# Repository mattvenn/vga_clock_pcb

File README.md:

Matt Venn's ASIC VGA Clock
==========================

* World's first [certified open source hardware](https://certification.oshwa.org/es000023.html) down to the GDS?
* The ASIC was part of the Google sponsored MPW1
* The ASIC is still in fabrication by Skywater, we expect silicon in September 2021.
* For more details about the implementation, see [VGA ASIC Clock](https://www.zerotoasiccourse.com/post/vga_clock/). 
* RTL: https://github.com/mattvenn/vga-clock
* Application details: https://efabless.com/projects/14

# PCB

This PCB provides all the necessary components to make a functional clock:

 * Pads for mounting the ASIC
 * Decoupling
 * Voltage regulators for core (1.8) and IO (3.3)
 * Crystal oscillator
 * SOIC-8 footprint for dual SPI flash for the configuration firmware
 * 2x6 1.27mm header with housekeeping SPI, UART and 5V - the minimum connection needed for power and debug
 * [PDF Schematic](rev0.1/carrier.pdf)

# Setup

## Firmware

Needs to active project 2. See https://github.com/mattvenn/caravel-mph/blob/release/verilog/dv/caravel/user_proj_example/vga-clock/vga_clock.c for the simulation test.
Will need PLL setup to work on the ASIC.

## Flashing

For flashing, see https://github.com/efabless/ravenna/blob/master/firmware/blink/Makefile as a starting point. ravenna_hkspi.py may need some tweaks to work with Caravel.

The [SPI interface can be used to put the ASIC into 'passthrough' mode](https://caravel-harness.readthedocs.io/en/latest/housekeeping-spi.html#housekeeping-spi-command-words). Then the FLASH can be programmed through this same SPI interface.

See the schematic for the pinout of the SPI interface on the board.

## PLL config

Needs 31.5MHz for VGA signal. As precise as possible for good timekeeping.
Input oscillator is 9MHz.

Using https://github.com/kbeckmann/caravel-pll-calculator

    matt-desktop:2003 [main]: ./caravel_pll.py generate --clkout 31.5 --clkin 9
    PLL Parameters:

    clkin:    9.00 MHz
    clkout:   31.50 MHz
    clkout90: 31.50 MHz

    PLL Feedback Divider: 14
    PLL Output Divider 1: 4
    PLL Output Divider 2: 4

    Register 0x11: 0x24
    Register 0x12: 0x0e

## Pinning

See the instantiation into the user project area here: https://github.com/mattvenn/multi-project-harness/blob/separate-macro/user_project_wrapper.v#L190
See the design repository here: https://github.com/mattvenn/vga-clock/tree/db029c38607c8d27f54b48bd8fd423cae3c4ed3d

    vga_clock proj_2 (
        .clk(proj2_clk),
        .reset_n(proj2_reset),
        .adj_hrs(proj2_io_in[8]),
        .adj_min(proj2_io_in[9]),
        .adj_sec(proj2_io_in[10]),
        .hsync(proj2_io_out[11]),
        .vsync(proj2_io_out[12]),
        .rrggbb(proj2_io_out[18:13])
        );

* rrggbb is mapped to R1, R2, G1, G2, B1, B2
* 500R used for R1, G1, B1
* 1k used for R2, G2, B2

## Power

### User project

* Power is provided to the clock design only by VCCD1 and VSSD1.
* Tim Edwards suggests:
    * keeping VCCD2 and VCCD1, VSSD2 and VSSD1 tied together just to make sure there are no floating power supplies.  
    * connect VDDA1 and VDDA2 to VDDIO, and VSSA1 and VSSA2 to VSSIO to make sure they're not floating.  
For reference, the power ring around the user project area has 4 buses. From outside to inside:  VSSA2, VDDA2, VSSA1, VDDA1, VSSD2, VCCD2, VSSD1, VCCD1.
    * VSSA2 user area 2 ground
    * VDDA2 3.3V user area 2 psu
    * VSSA1 user area 1 ground
    * VDDA1 3.3V user area 1 psu
    * VSSD2 user area 2 digital ground
    * VCCD2 1.8V user area 2 digital psu
    * VSSD1 user area 1 digital ground
    * VCCD1 1.8V user area 1 digital psu

### Management

* VDDIO/VSSIO   power and ground for IO (up to 5v). I'm connecting to 3.3v
* VDDA/VSSA     3.3v PSU for management area
* VCCD/VSSD     1.8v PSU for management area

# BOM

All available from digikey as of 13/7/21

* regulators
    * 1.8v MCP1824T-1802E/OT
    * 3.3v MIC5504-3.3YM5-TR
* flash: W25Q32JVSSIQ-TR
* oscillator: SIT8008AI-23-33S-9.000000 
* VGA connector: L77HDE15SD1CH4F
* USB connector: 1050170001
* buttons: PTS636 SM25J SMTR LFS

# Errata

## v0.1

* Initial footprint for ASIC was flipped. 
* All other components were tested and worked as expected.

## v0.2

* TBD

# Resources

* PCB forked from https://github.com/samlittlewood/caravel_carrier
* Caravel datasheet: https://caravel-harness.readthedocs.io/en/latest
* Logo created at: http://oshwmark.capablerobot.com/
* PCBs sponsored by https://OSHPark.com

# License

* The PCB is licensed under the [MIT License](LICENSE)
* The ASIC is licensed under the [Apache2 License](https://github.com/mattvenn/vga-clock/blob/master/LICENSE-2.0.txt)
* The documentation is licensed under the [CC0 License](CC0_license)

# Open Source Hardware

This board is an OSHWA approved design: [ES000023](https://certification.oshwa.org/es000023.html)

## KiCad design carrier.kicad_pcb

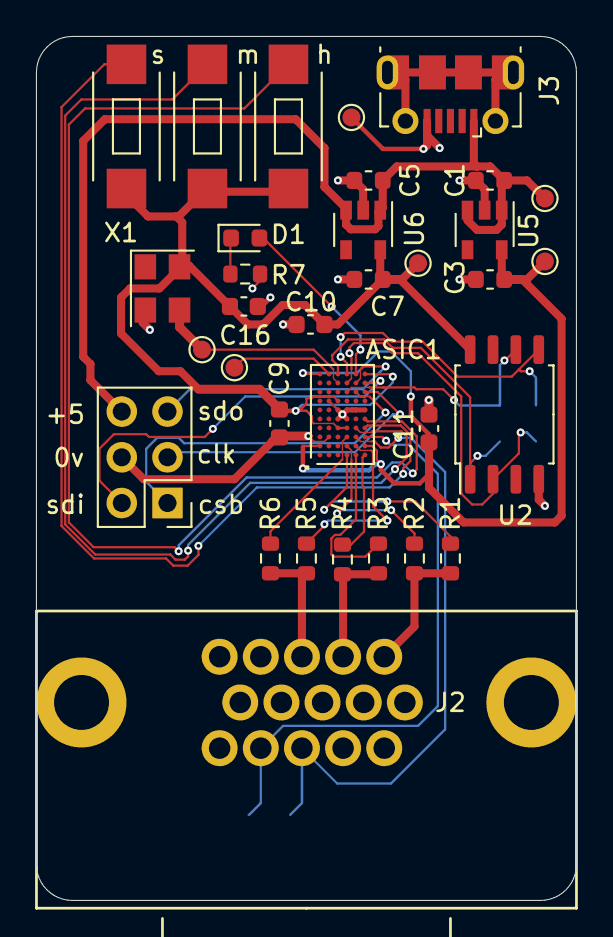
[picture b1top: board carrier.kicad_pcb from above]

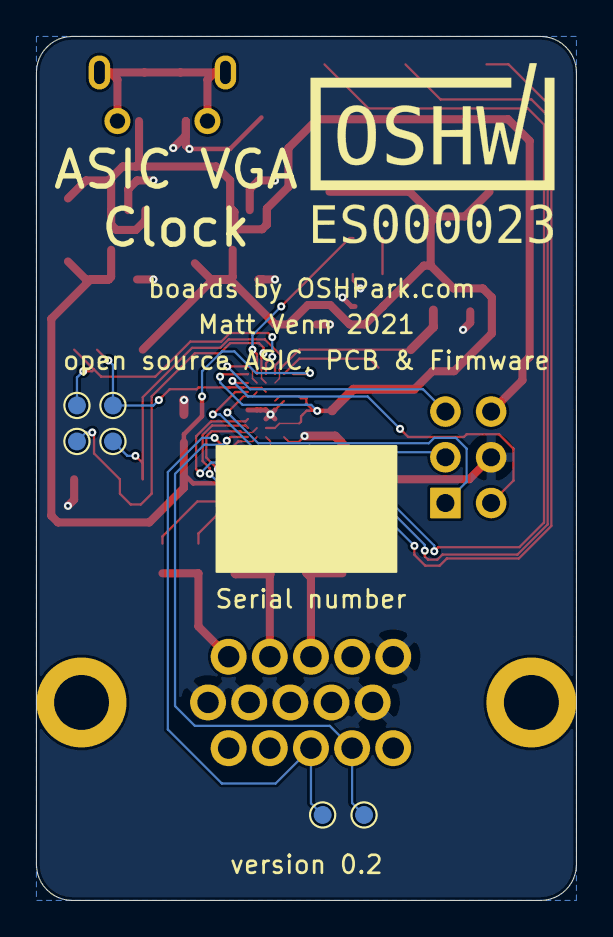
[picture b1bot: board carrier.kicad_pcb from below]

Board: 2 copper layers, 30.0 x 48.0 mm, 39 parts (6 on the bottom side), 30 nets.

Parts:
ASIC1: CARAVEL; WLCSP-60_P0.5mm
C1, C5: 1u 16v; C_0603_1608Metric
C3, C7: 4u7 16v; C_0603_1608Metric
C9, C10, C11, C16: 22n; C_0603_1608Metric
D1: LED; LED_0603_1608Metric
J1: Conn_02x03_Counter_Clockwise; PinHeader_2x03_P2.54mm_Vertical
J2: DB15_Female_HighDensity; db15
J3: USB_B_Micro; USB_Micro-B_Molex-105017-0001
R1, R3, R5: 500R; R_0603_1608Metric
R2, R4, R6: 1k; R_0603_1608Metric
R7: 100R; R_0603_1608Metric
SW1: SW_Push_hrs; pts636
SW2: SW_Push_min; pts636
SW3: SW_Push_sec; pts636
TP1, TP2, TP3, TP4, TP5, TP6, TP7, TP8, TP9, TP10, TP11, TP12: TestPoint; TestPoint_Pad_D1.0mm
U2: W25Q32JVSSIQ-TR; SOIC-8_5.23x5.23mm_P1.27mm
U5: MCP1824T-1802E/OT; SOT-23-5
U6: MIC5504-3.3YM5-TR; SOT-23-5
X1: ECS-5032MV-100-BN-TR; Oscillator_SMD_SeikoEpson_SG8002CE-4Pin_3.2x2.5mm

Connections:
+5V: C1.1, C5.1, J1.6, J3.1, TP10.1, U5.1, U5.3, U6.1, U6.3
/blue: J2.3, R5.1, R6.1
/green: J2.2, R3.1, R4.1
/red: J2.1, R1.1, R2.1
GND: ASIC1.B3, ASIC1.B7, ASIC1.C5, ASIC1.C6, ASIC1.D5, ASIC1.D6, ASIC1.E6, ASIC1.F6, C1.2, C3.2, C5.2, C7.2, C9.2, C10.2, C11.2, C16.2, J1.4, J2.5, J2.6, J2.7, J2.8, J2.10, J3.5, R7.2, TP12.1, U2.4, U5.2, U6.2, X1.2
unnamed: D1.1, R7.1
clock: ASIC1.C9, TP6.1, X1.3
flash_clk: ASIC1.D8, TP2.1, U2.6
flash_csb: ASIC1.C10, TP3.1, U2.1
flash_io0: ASIC1.D10, TP4.1, U2.5
flash_io1: ASIC1.D9, TP5.1, U2.2
gpio: ASIC1.E10, D1.2
mprj_io[1]: ASIC1.E9, J1.5
mprj_io[2]: ASIC1.F9, J1.2
mprj_io[3]: ASIC1.E8, J1.1
mprj_io[4]: ASIC1.F8, J1.3
mprj_io[8]: ASIC1.F5, SW1.1
mprj_io[9]: ASIC1.E4, SW2.1
mprj_io[10]: ASIC1.F4, SW3.1
mprj_io[11]: ASIC1.E3, J2.13, TP7.1
mprj_io[12]: ASIC1.F3, J2.14, TP8.1
mprj_io[13]: ASIC1.D3, R6.2
mprj_io[14]: ASIC1.E2, R5.2
mprj_io[15]: ASIC1.F1, R4.2
mprj_io[16]: ASIC1.E1, R3.2
mprj_io[17]: ASIC1.D2, R2.2
mprj_io[18]: ASIC1.D1, R1.2
resetb: ASIC1.B10, TP1.1
vccd: ASIC1.A2, ASIC1.A10, ASIC1.F2, C3.1, C11.1, TP9.1, U5.5
vdda: ASIC1.C4, ASIC1.C7, ASIC1.D4, ASIC1.F10, C7.1, C9.1, C10.1, C16.1, SW1.2, SW2.2, SW3.2, TP11.1, U2.8, U6.5, X1.4

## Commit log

2020-11-21 Add kicad files.
2020-11-21 Added README
2020-11-21 Missing files.
2020-11-21 Fix README.
2020-11-21 Add note about JLCPCB.
2020-11-23 Tidy up and ground pours.
2020-11-23 Updated plots.
2020-11-23 Tidy up regulators.
2020-11-23 Flipped to have regulators at top, makes pin/io number a better match.
2020-11-23 Tidy up power routing.
2020-11-23 Tidy up oscillator.
2020-11-23 Solder mask clearance.
2020-11-24 Use 1.27mm header.
2020-11-27 Clean up clearances.
2020-12-18 Use 5mil for inner layers.
2020-12-18 Correct directions on global labels.
2020-12-20 Update gerbers & pdf.
2020-12-23 Make wlcsp escape 3mil/3mil.
2020-12-23 Made rest of board 4mil/4mil.
2020-12-23 New output files.
2021-04-17 Update README.md
    make it more discoverable with searches. I tried all variants of pcb, shuttle, asic, caravel, efabless and couldn't find it!
2021-07-06 updating for vga clock
2021-07-06 fp for vga
2021-07-06 pdf of schematic
2021-07-06 updated pcb
2021-07-06 format
2021-07-06 docs and license. fix db15 fp, add oshw logo
2021-07-06 include pics
2021-07-06 pics
2021-07-06 gerbers
2021-07-06 questions
2021-07-06 routing and silk improvements, added an led to GPIO
2021-07-06 updated pdf
2021-07-06 DAC ladder updated
2021-07-06 continue to tweak layout
2021-07-13 all BOM parts found on digikey, button footprint
2021-07-23 ES000023 OSHW registration
2021-07-23 updated board with OSHW mark
2021-07-23 new render
2021-07-27 update boards from Drews render
2021-07-27 oshpark link and remove question
2021-07-27 both sides...
2021-07-27 notes
2021-07-27 link
2021-07-27 link to RTL
2021-07-28 update gerbers
2021-07-29 switch to 3.2x2.5 9mhz oscillator, only use 3/3 right under ASIC
2021-07-29 changed programming header to 2x3
2021-08-11 test points, added managment area psu notes to readme
2021-08-11 missing oshwa logo
2021-09-03 ordered from oshpark
2021-09-15 render update
2021-09-23 flip footprint
2021-09-23 flip the silk as well
2021-09-23 updated to correct asic fp
2021-09-24 rev0.2 gerber
2021-09-24 fix flipped asic fp, updated to v0.2, added ground testpad, added silk version, notes on testing the regs and clock
